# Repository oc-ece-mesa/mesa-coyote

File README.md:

# MESA Coyote

<div>

</div>

Coyote is a handheld game system that uses the MESA Basalt devboard.

The case for the Coyote is called "Roadrunner" and can be found [here](https://github.com/oc-ece-mesa/mesa-roadrunner).

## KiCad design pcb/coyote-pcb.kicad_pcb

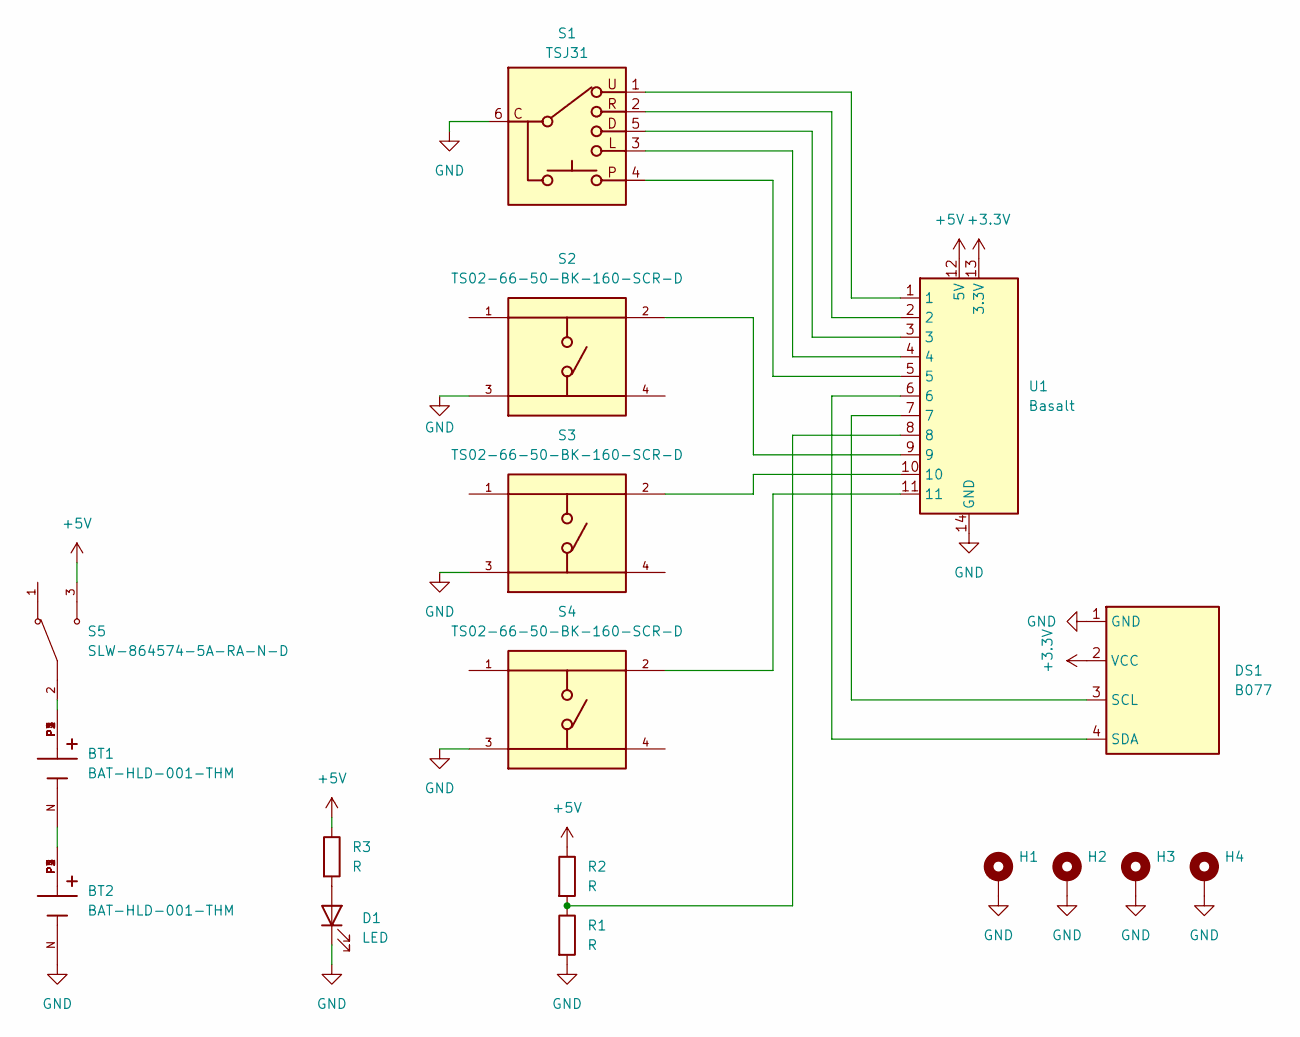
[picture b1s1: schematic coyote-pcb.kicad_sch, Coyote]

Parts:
BT1, BT2: BAT-HLD-001-THM; BAT_BAT-HLD-001-THM
D1: LED; LED_D3.0mm
DS1: B077
H1, H2, H3, H4: MountingHole_Pad; MountingHole_3.2mm_M3_Pad
R1, R2, R3: R; R_Axial_DIN0309_L9.0mm_D3.2mm_P12.70mm_Horizontal
S1: TSJ31
S2, S3, S4: TS02-66-50-BK-160-SCR-D; SW_TS02-66-50-BK-160-SCR-D; PARTREV 1.0
S5: SLW-864574-5A-RA-N-D; SW_SLW-864574-5A-RA-N-D; PARTREV 1.01
U1: Basalt; MESA_Basalt_RevA

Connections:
+3.3V: DS1.2 (VCC), U1.13 (3.3V)
+5V: R2.1, R3.1, S5.3, U1.12 (5V)
GND: BT2.N, D1.1 (K), DS1.1 (GND), H1.1 (1_1), H2.1 (1_1), H3.1 (1_1), H4.1 (1_1), R1.2, S1.6 (COMMON), S2.3, S3.3, S4.3, U1.14 (GND)
unnamed: BT1.N, BT2.P1, BT2.P2, BT2.P3, BT2.P4
unnamed: BT1.P1, BT1.P2, BT1.P3, BT1.P4, S5.2
unnamed: D1.2 (A), R3.2
unnamed: DS1.3 (SCL), U1.7
unnamed: DS1.4 (SDA), U1.6
unnamed: R1.1, R2.2, U1.8
unnamed: S1.5 (DOWN), U1.3
unnamed: S1.3 (LEFT), U1.4
unnamed: S1.4 (PRESS), U1.5
unnamed: S1.2 (RIGHT), U1.2
unnamed: S1.1 (UP), U1.1
unnamed: S2.2, U1.9
unnamed: S3.2, U1.10
unnamed: S4.2, U1.11

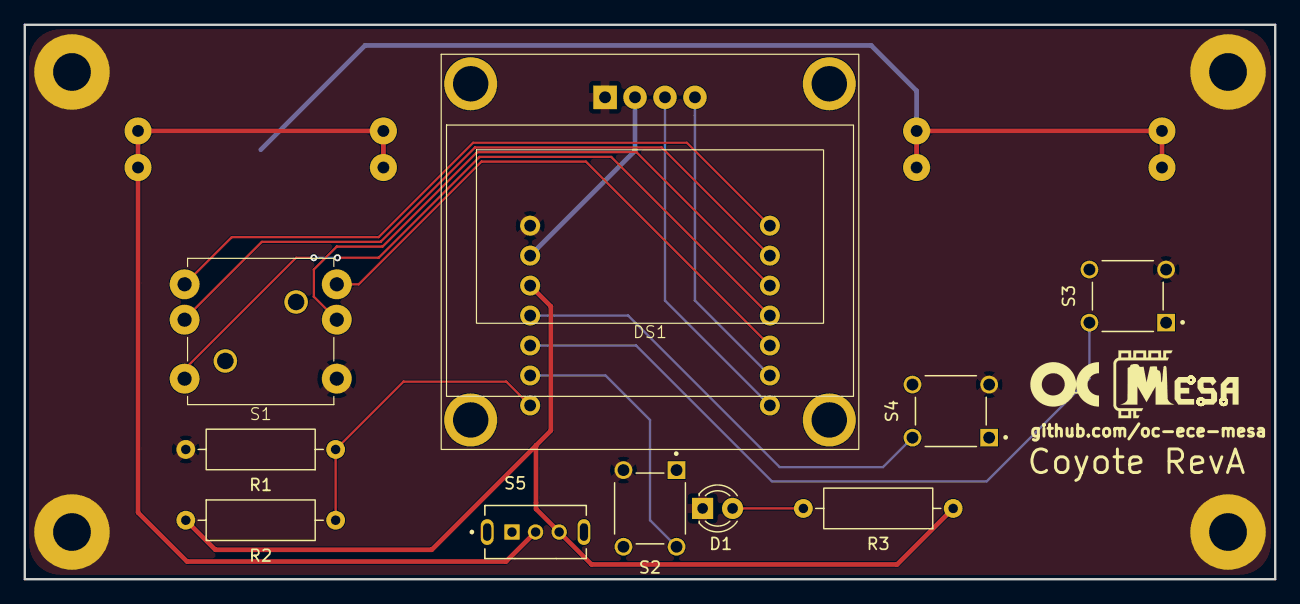
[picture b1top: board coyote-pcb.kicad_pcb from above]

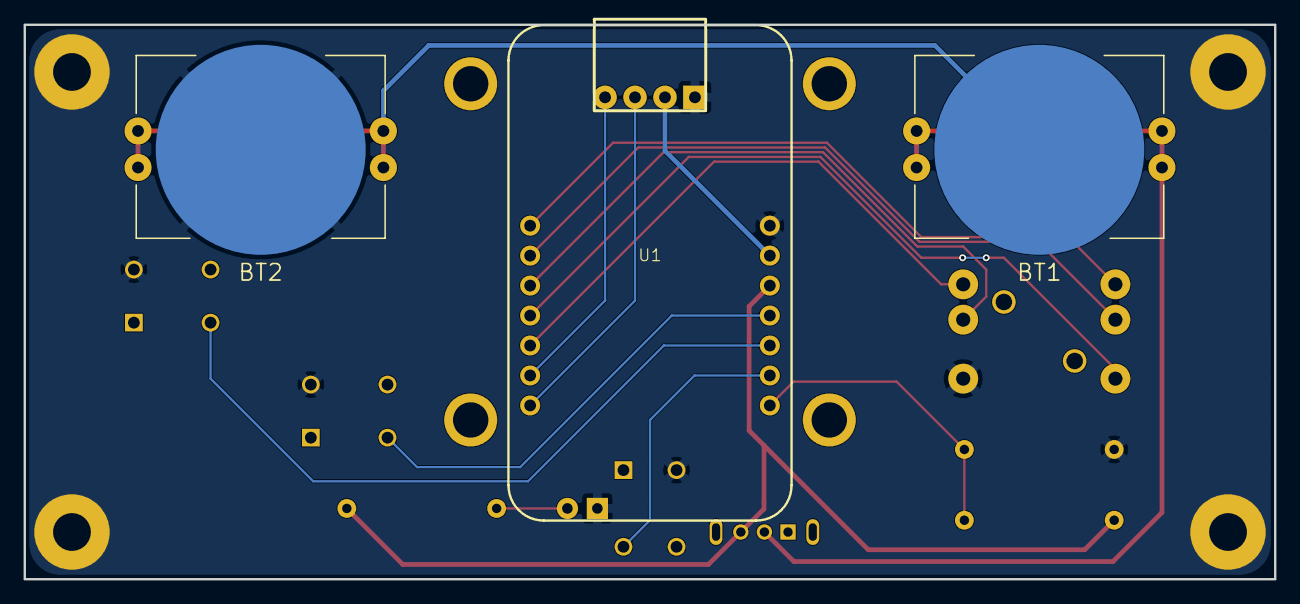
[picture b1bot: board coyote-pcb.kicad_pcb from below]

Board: 2 copper layers, 106.0 x 47.0 mm, 17 parts (3 on the bottom side), 17 nets.

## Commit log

2026-04-25 First full pass at design. Update gitignore.
2026-04-30 Update with new Basalt design
2026-05-04 Lots of small updates
2026-05-04 Add 3D models for most parts
2026-05-07 Add nav switch model. Update gitignore.
2026-05-10 Add silkscreen logo etc, update title blocks
2026-05-10 Update output folders
2026-06-07 Add dimensional drawing and STEP file
2026-06-14 Add images
2026-06-14 Make images bigger
